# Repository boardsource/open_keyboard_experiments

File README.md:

# Open Keyboard Experiments.

So as we design keyboards we at Boardsource try out a lot of things.
Most of these things never see the light of day.
Now instead of letting them rot on a hard drive I thought it would be cool to let others see what we were paying with and maybe take learning.

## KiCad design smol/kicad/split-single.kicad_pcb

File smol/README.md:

# smol

## Story time.

I thought I would tell you why we made this board.
I read A LOT of keyboard stuff day to day, one day I was reading about how much some people find the 100x100mm $2 pcbs very important to the hobby.
That made me remember back years ago when I first got into custom ergo boards how thats where I cut my teeth.
So I wanted to give back to this awesome community by making another cheap board.

I also was reading about [square matrixes](https://kbd.news/Square-or-round-robin-matrix-1400.html), this all came together into this keyboard.
This keyboard is 1 pcb that flips to make the full single piece board.
It is a symmetric staggered keyboard using 2 square matrixes with pcbs under 100x100mm,
choc spaced with a 3d printed case that comes pre supported,for fdm printing or you can order them from jlc pcb at $1.68.

you only need:

- 1 controller
- 36 choc switches & caps
- 41 diodes
- 2 pcbs
- 2 cases

# Disclaimer

There is no code support for this.
In the firmware section there is kmk code until the pr is finished.
I think you need a custom matrix.c in qmk to use this keyboard.
Depending on your diodes and controller selection this keyboard may not work.
Its tested with normal diodes with Blok controller.
I dont think elite-c's would work being that they are 5V.
I included pin holes but have not tested n!n.

For most extra you can use [BS-python](https://github.com/boardsource/bs-python) our fork of circuitpython it has the matrix code frozen in,along with all of kmk. meaning you can simply drag on main.py and kb.py.

I will try to make sure there is a up-to-date ready to order gerber in the kicad/gerber folder so people can download and order.

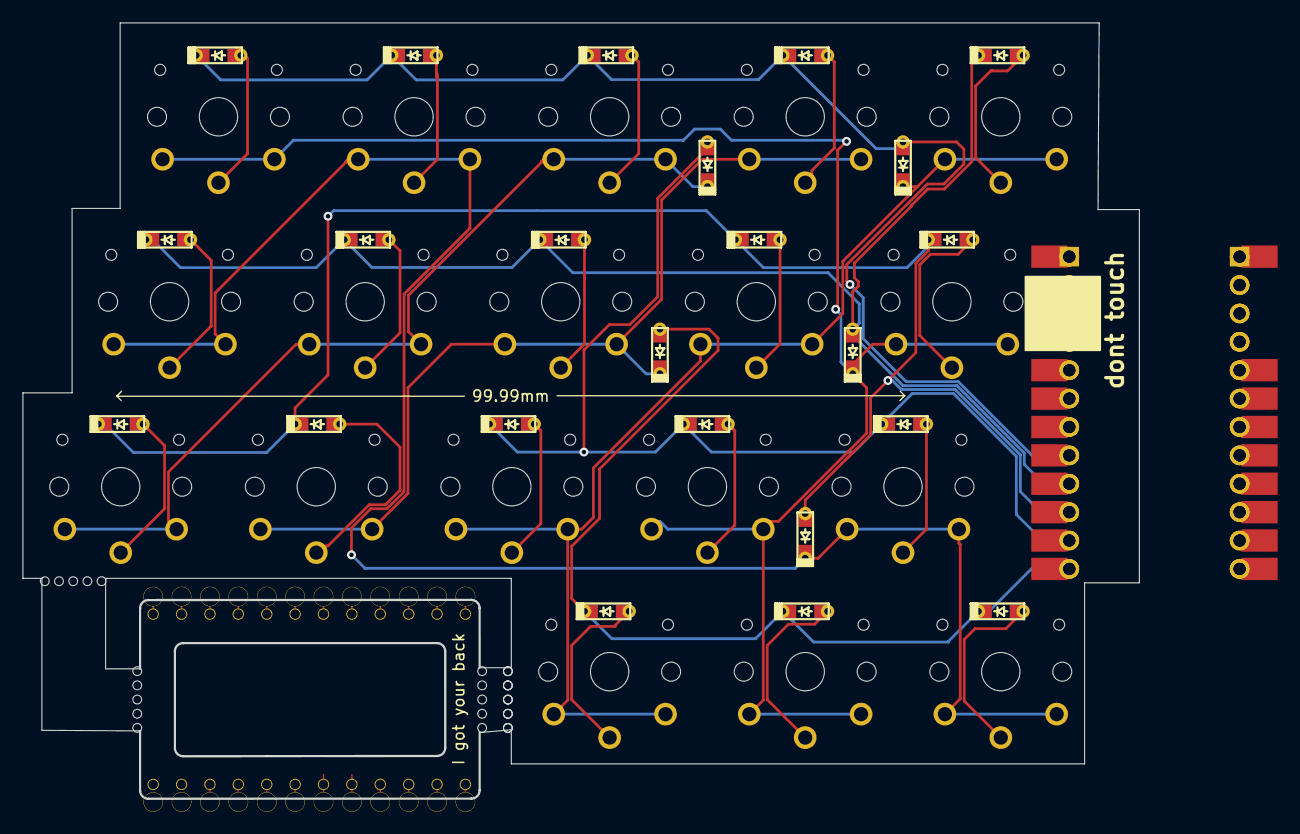
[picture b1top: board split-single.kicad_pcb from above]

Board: 2 copper layers, 99.9 x 69.4 mm, 46 parts (1 on the bottom side), 50 nets.

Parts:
D1, D2, D3, D4, D5, D6, D7, D8, D9, D10, D11, D12, D13, D14, D15, D16, D17, D18, D19, D21, D22, D23, D25: D_Small; D_SOD123F_dual
FRAME2: FRAME-LEDGER; CREATIVE_COMMONS
J3, J4: CONN_12CASTLE; 1X12_CASTELLATED
SW1, SW2, SW3, SW4, SW5, SW6, SW7, SW8, SW9, SW10, SW11, SW12, SW13, SW14, SW15, SW17, SW18, SW19: SW_PUSH; SW_PG1350_reversible
U1, U2: ProMicro; Elite-C-castellated-24pin-holes

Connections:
3.3V: J4.4, J4.4B
/0/TX0: J3.12, J3.12B
/1/RX0: J3.11, J3.11B
/4: J3.6, J3.6B
/5: J3.5, J3.5B
/6: J3.4, J3.4B
/7: J3.3, J3.3B
/8/TX1: J3.2, J3.2B
/9/RX1: J3.1, J3.1B
/16/SDA: J3.8, J3.8B
/17/SCL: J3.7, J3.7B
/20/SPI_CIPO: J4.10, J4.10B
/21/SPI_~CS: J4.12, J4.12B
/22/SPI_SCK: J4.9, J4.9B
/23/SPI_COPI: J4.11, J4.11B
/A0: J4.8, J4.8B
/A1: J4.7, J4.7B
/A2: J4.6, J4.6B
/A3: J4.5, J4.5B
/RAW: J4.1, J4.1B
/~RESET: J4.3, J4.3B
GND: J3.9, J3.9B, J3.10, J3.10B, J4.2, J4.2B
unnamed: D1.1 (K), SW5.2, SW9.2, SW13.2, SW17.2
unnamed: D2.2 (A), SW1.1
unnamed: D3.2 (A), SW2.1
unnamed: D4.2 (A), SW3.1
unnamed: D5.2 (A), SW4.1
unnamed: D6.2 (A), SW5.1
unnamed: D7.1 (K), SW1.2, SW10.2, SW14.2, SW18.2
unnamed: D8.2 (A), SW6.1
unnamed: D9.2 (A), SW7.1
unnamed: D10.2 (A), SW8.1
unnamed: D11.2 (A), SW9.1
unnamed: D12.2 (A), SW10.1
unnamed: D13.1 (K), SW2.2, SW6.2, SW15.2, SW19.2
unnamed: D14.2 (A), SW11.1
unnamed: D15.2 (A), SW12.1
unnamed: D16.2 (A), SW13.1
unnamed: D17.2 (A), SW14.1
unnamed: D18.2 (A), SW15.1
unnamed: D19.1 (K), SW3.2, SW7.2, SW11.2
unnamed: D21.2 (A), SW17.1
unnamed: D22.2 (A), SW18.1
unnamed: D23.2 (A), SW19.1
unnamed: D25.1 (K), SW4.2, SW8.2, SW12.2
pin0: D1.2 (A), D2.1 (K), D3.1 (K), D4.1 (K), D5.1 (K), U1.8 (5/C6), U1.17 (F7/A0), U2.8 (5/C6), U2.17 (F7/A0)
pin1: D6.1 (K), D7.2 (A), D8.1 (K), D9.1 (K), D10.1 (K), U1.9 (6/D7), U1.16 (B1/15), U2.9 (6/D7), U2.16 (B1/15)
pin2: D11.1 (K), D12.1 (K), D13.2 (A), D14.1 (K), D15.1 (K), U1.10 (7/E6), U1.15 (B3/14), U2.10 (7/E6), U2.15 (B3/14)
pin3: D16.1 (K), D17.1 (K), D18.1 (K), D19.2 (A), U1.11 (8/B4), U1.14 (B2/16), U2.11 (8/B4), U2.14 (B2/16)
pin4: D21.1 (K), D22.1 (K), D23.1 (K), D25.2 (A), U1.12 (9/B5), U1.13 (B6/10), U2.12 (9/B5), U2.13 (B6/10)

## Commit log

2023-03-31 smol keyboard
2023-03-31 links
2023-03-31 added case
2023-03-31 gerber note
2023-04-03 readme more
2023-04-09 readme
